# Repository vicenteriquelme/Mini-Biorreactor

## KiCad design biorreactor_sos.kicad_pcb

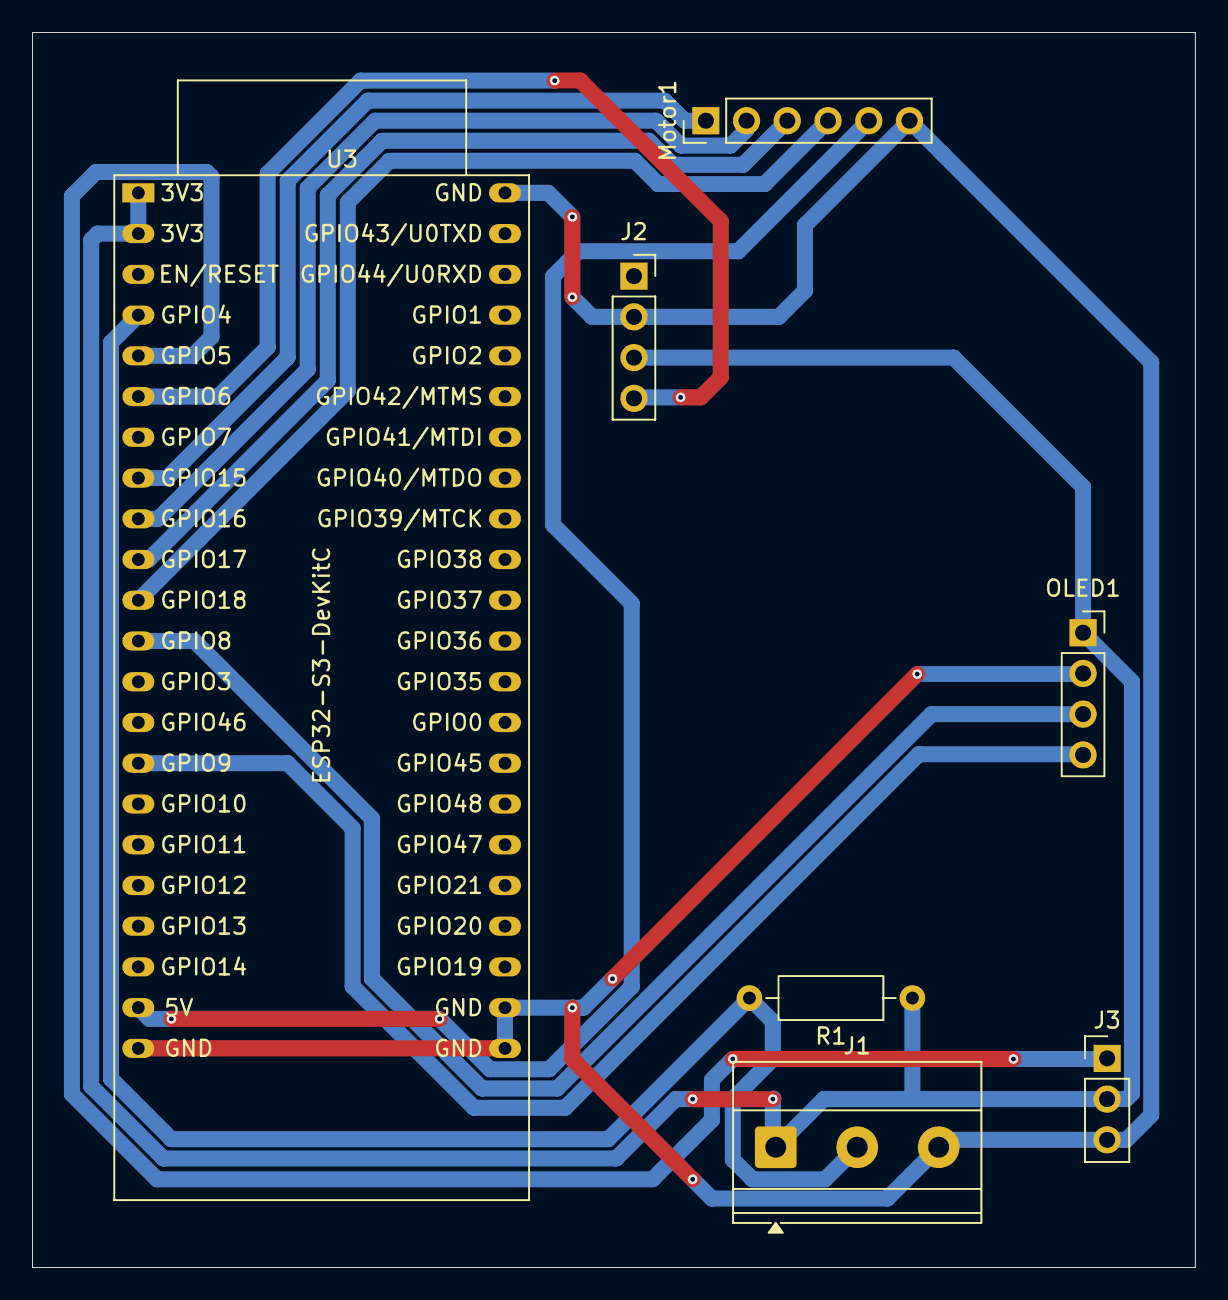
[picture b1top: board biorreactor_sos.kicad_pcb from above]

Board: 2 copper layers, 72.5 x 77.0 mm, 7 parts (0 on the bottom side), 12 nets.

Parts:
J1: Temperature sensor; TerminalBlock_Phoenix_MKDS-1,5-3-5.08_1x03_P5.08mm_Horizont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
J2: KY-024; PinSocket_1x04_P2.54mm_Vertical
J3: pH Meter; PinHeader_1x03_P2.54mm_Vertical
Motor1: ULN2003_Module; PinHeader_1x06_P2.54mm_Vertical
OLED1: OLED 1.3''; PinSocket_1x04_P2.54mm_Vertical
R1: 4.7k; R_Axial_DIN0207_L6.3mm_D2.5mm_P10.16mm_Horizontal
U3: ESP32-S3-DevKitC

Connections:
/+3V3: J1.1, J2.3, J3.2, OLED1.1, R1.1, U3.1 (3V3), U3.2 (3V3)
/+5V: Motor1.5, U3.21 (5V)
/A: J3.1, U3.5 (GPIO5/ADC1_CH4)
/D0: J2.4, U3.6 (GPIO6/ADC1_CH5)
/GND: J1.3, J2.2, J3.3, Motor1.6, OLED1.2, U3.22 (GND), U3.23 (GND), U3.24 (GND), U3.44 (GND)
/IN1: Motor1.1, U3.8 (GPIO15/ADC2_CH4/32K_P)
/IN2: Motor1.2, U3.9 (GPIO16/ADC2_CH5/32K_N)
/IN3: Motor1.3, U3.10 (GPIO17/ADC2_CH6)
/IN4: Motor1.4, U3.11 (GPIO18/ADC2_CH7)
/SCK: OLED1.3, U3.12 (GPIO8/ADC1_CH7)
/SDA: OLED1.4, U3.15 (GPIO9/ADC1_CH8)
/TEMP: J1.2, R1.2, U3.4 (GPIO4/ADC1_CH3)
